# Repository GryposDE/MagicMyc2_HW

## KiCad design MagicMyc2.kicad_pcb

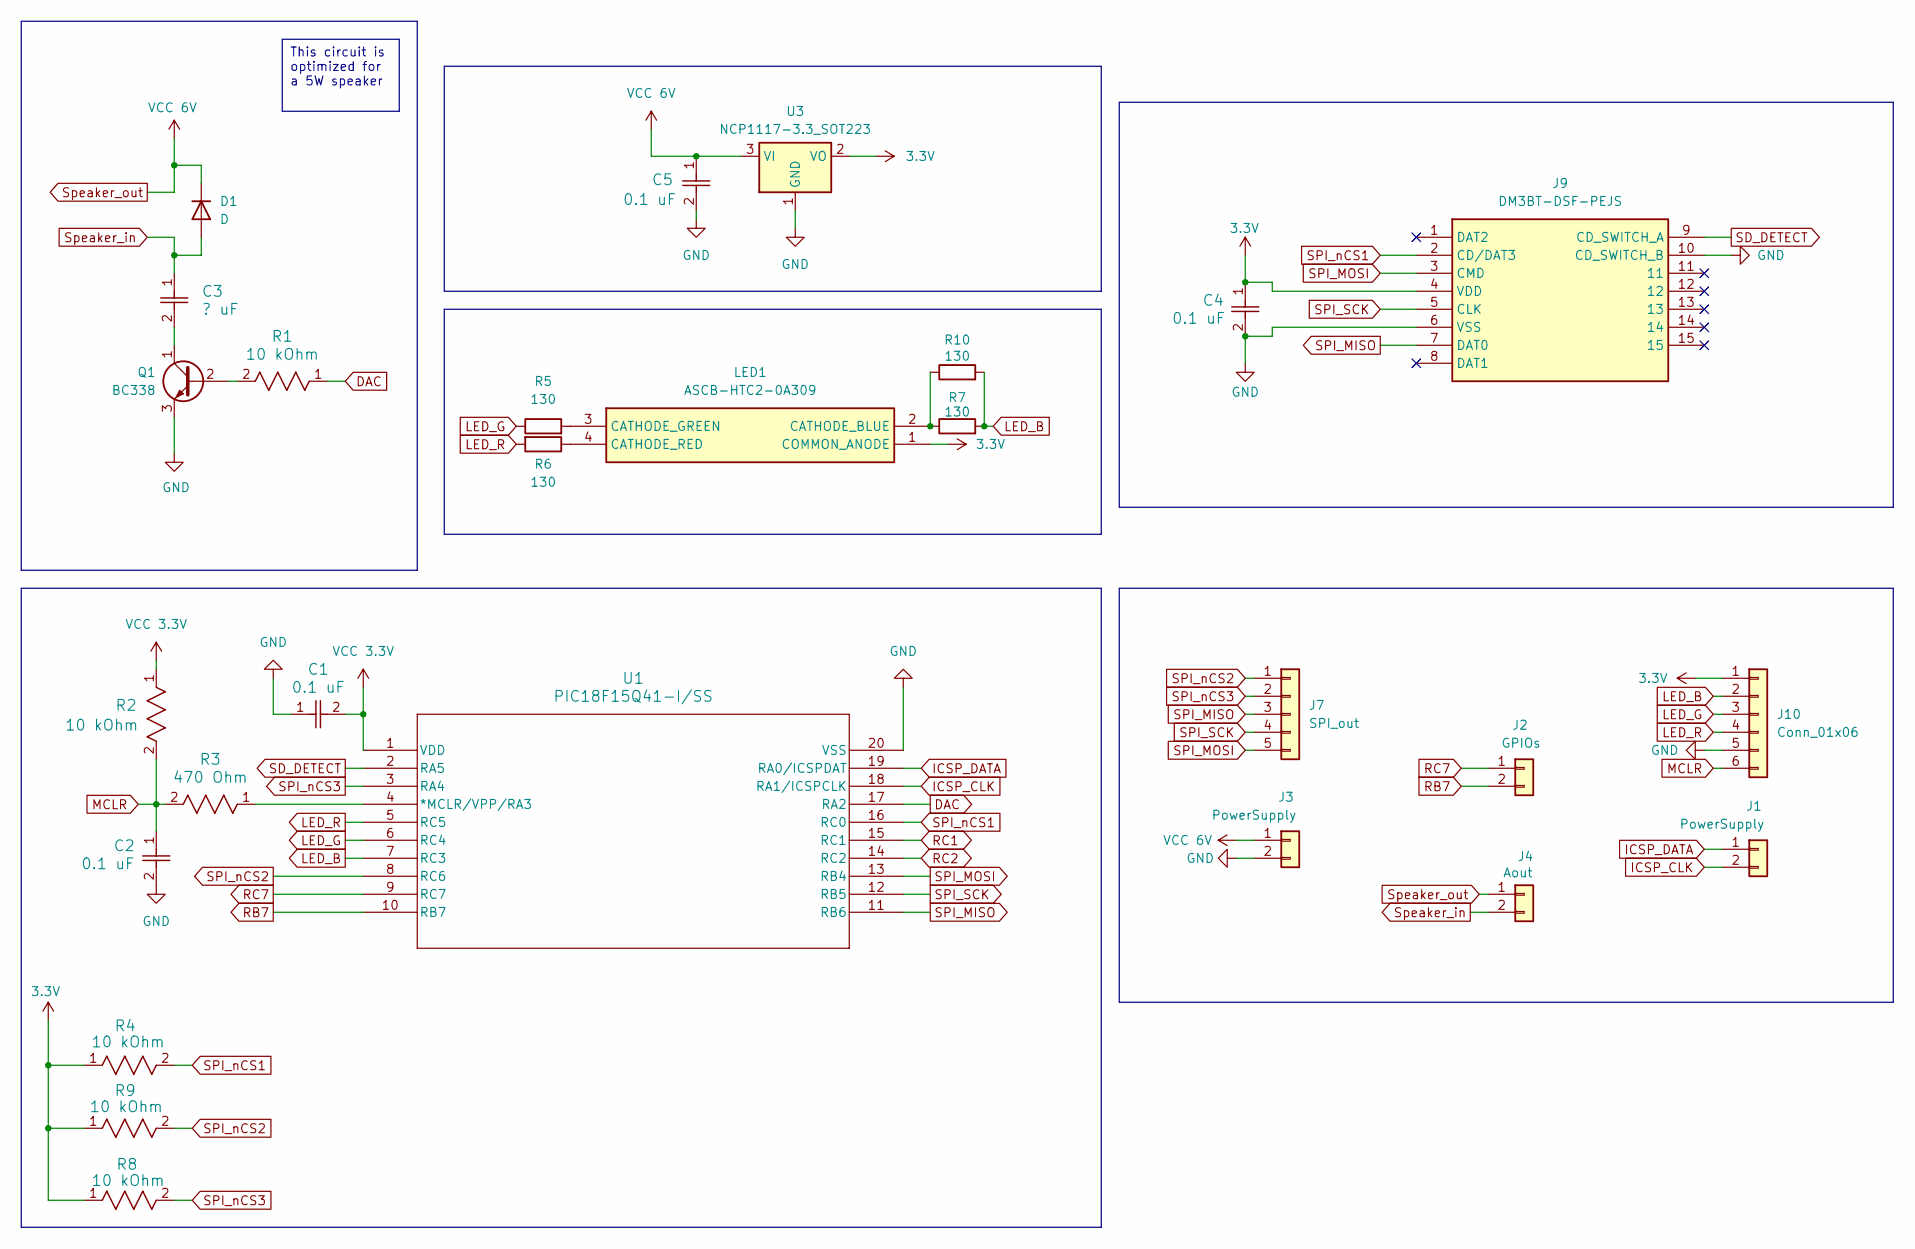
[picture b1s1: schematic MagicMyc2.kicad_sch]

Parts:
C1, C2, C4, C5: 0.1 uF; CAPC17595_87N_KEM
C3: ? uF; CAPC17595_87N_KEM
D1: D; D_0603_1608Metric_Pad1.05x0.95mm_HandSolder
J1, J3: PowerSupply; PinHeader_1x02_P2.00mm_Vertical
J2: GPIOs; PinHeader_1x02_P2.00mm_Vertical
J4: Aout; PinHeader_1x02_P2.00mm_Vertical
J7: SPI_out; PinHeader_1x05_P2.00mm_Vertical
J9: DM3BT-DSF-PEJS; microSD_HC_Hirose_DM3BT-DSF-PEJS; Mouser Part Number 798-DM3BT-DSF-PEJS
J10: Conn_01x06; PinHeader_1x06_P2.00mm_Vertical
LED1: ASCB-HTC2-0A309; ASCBHTC20A309; Mouser Part Number 630-ASCB-HTC2-0A309
Q1: BC338; TO-92_Inline
R1, R2, R4, R8, R9: 10 kOhm; RC0603N_YAG
R3: 470 Ohm; RC0402N_YAG
R5, R6, R7, R10: 130; R_0603_1608Metric
U1: PIC18F15Q41-I/SS; SSOP20_SS_MCH
U3: NCP1117-3.3_SOT223; SOT-223-3_TabPin2

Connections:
3.3V: C4.1, J9.4 (VDD), J10.1, LED1.1 (COMMON_ANODE), R4.1, R8.1, R9.1, U3.2 (VO)
DAC: R1.1, U1.17 (RA2)
GND: C1.1, C2.2, C4.2, C5.2, J3.2, J9.6 (VSS), J9.10 (CD_SWITCH_B), J10.5, Q1.3 (E), U1.20 (VSS), U3.1 (GND)
ICSP_CLK: J1.2, U1.18 (RA1/ICSPCLK)
ICSP_DATA: J1.1, U1.19 (RA0/ICSPDAT)
LED_B: J10.2, R7.2, R10.2, U1.7 (RC3)
LED_G: J10.3, R5.1, U1.6 (RC4)
LED_R: J10.4, R6.2, U1.5 (RC5)
MCLR: C2.1, J10.6, R2.2, R3.2
unnamed: LED1.2 (CATHODE_BLUE), R7.1, R10.1
unnamed: LED1.3 (CATHODE_GREEN), R5.2
unnamed: LED1.4 (CATHODE_RED), R6.1
unnamed: Q1.2 (B), R1.2
unnamed: C3.2, Q1.1 (C)
unnamed: R3.1, U1.4 (*MCLR/VPP/RA3)
RB7: J2.2, U1.10 (RB7)
RC1: U1.15 (RC1)
RC2: U1.14 (RC2)
RC7: J2.1, U1.9 (RC7)
SD_DETECT: J9.9 (CD_SWITCH_A), U1.2 (RA5)
SPI_MISO: J7.3, J9.7 (DAT0), U1.11 (RB6)
SPI_MOSI: J7.5, J9.3 (CMD), U1.13 (RB4)
SPI_SCK: J7.4, J9.5 (CLK), U1.12 (RB5)
SPI_nCS1: J9.2 (CD/DAT3), R4.2, U1.16 (RC0)
SPI_nCS2: J7.1, R9.2, U1.8 (RC6)
SPI_nCS3: J7.2, R8.2, U1.3 (RA4)
Speaker_in: C3.1, D1.2 (A), J4.2
Speaker_out: C5.1, D1.1 (K), J3.1, J4.1, U3.3 (VI)
VCC 3.3V: C1.2, R2.1, U1.1 (VDD)

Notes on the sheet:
This circuit is optimized for a 5W speaker

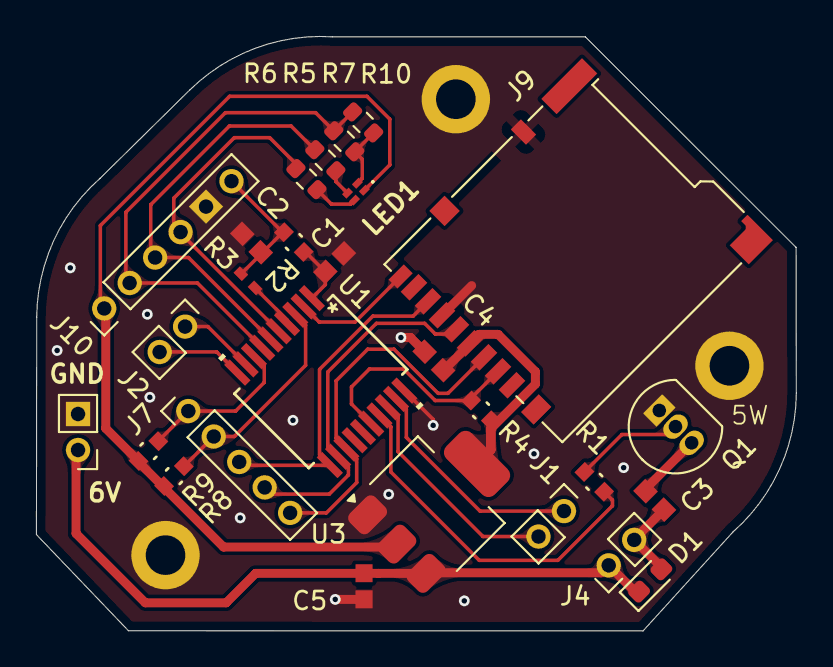
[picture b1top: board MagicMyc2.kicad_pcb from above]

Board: 2 copper layers, 42.2 x 33.0 mm, 27 parts (0 on the bottom side), 27 nets.

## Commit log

2025-01-25 v2: changed Pinout, Layout; removed 6V PG-LED
2025-01-26 added drill holes back
2025-01-26 Updated schematic pdf + some 3D models
2025-02-13 Added design optimizations + Removed little ground islands by increasing min area size + Added teardrops + Fixes (almost) all errors + Added another 130Ohm resistor for RGB-LED (green) to maximize gr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
2025-02-15 Added rounded corners
